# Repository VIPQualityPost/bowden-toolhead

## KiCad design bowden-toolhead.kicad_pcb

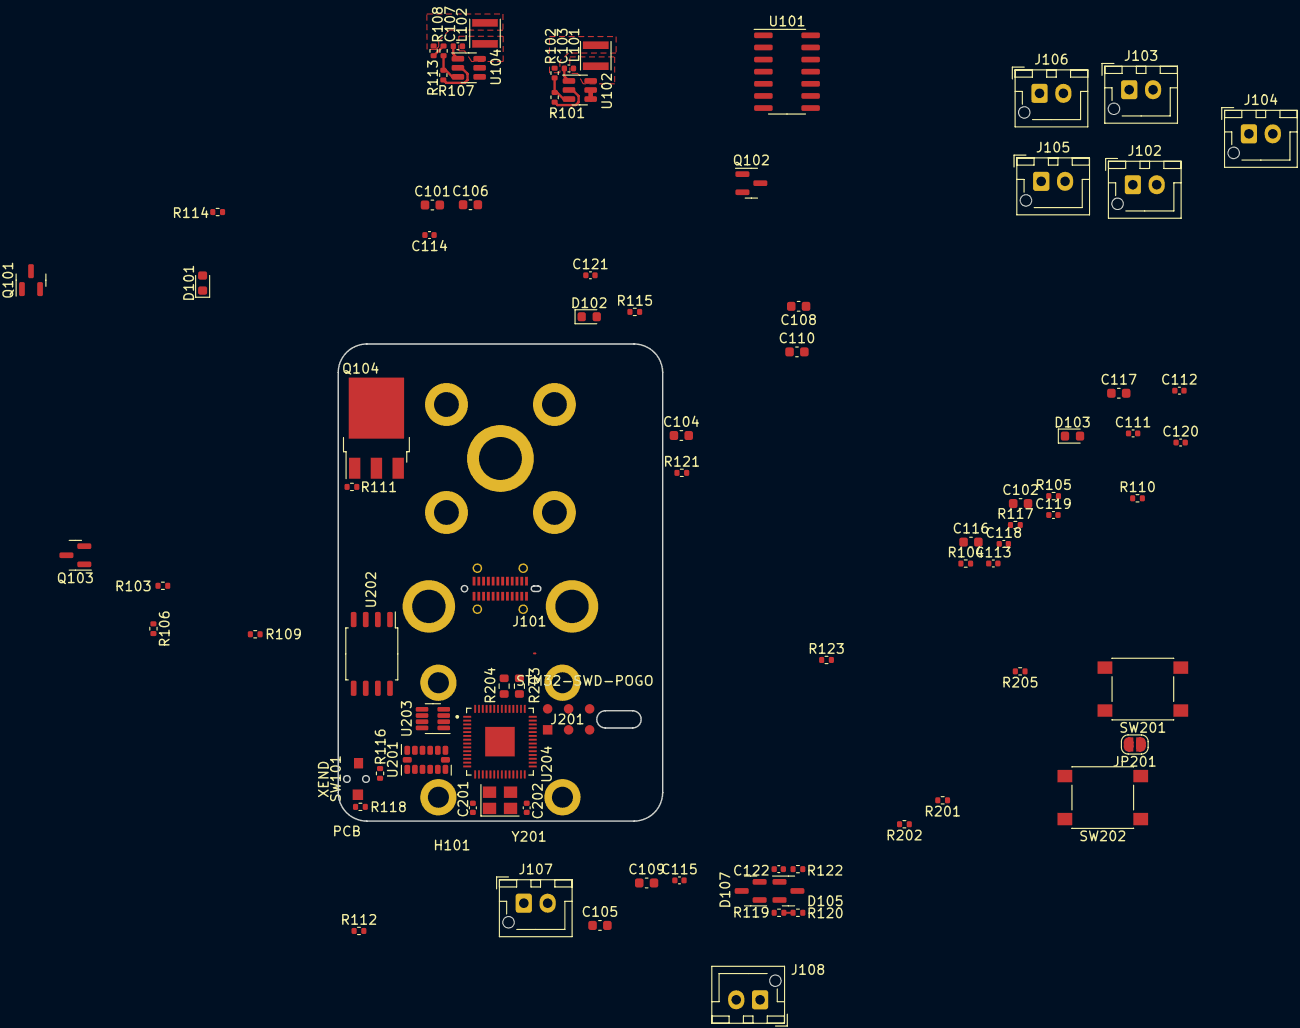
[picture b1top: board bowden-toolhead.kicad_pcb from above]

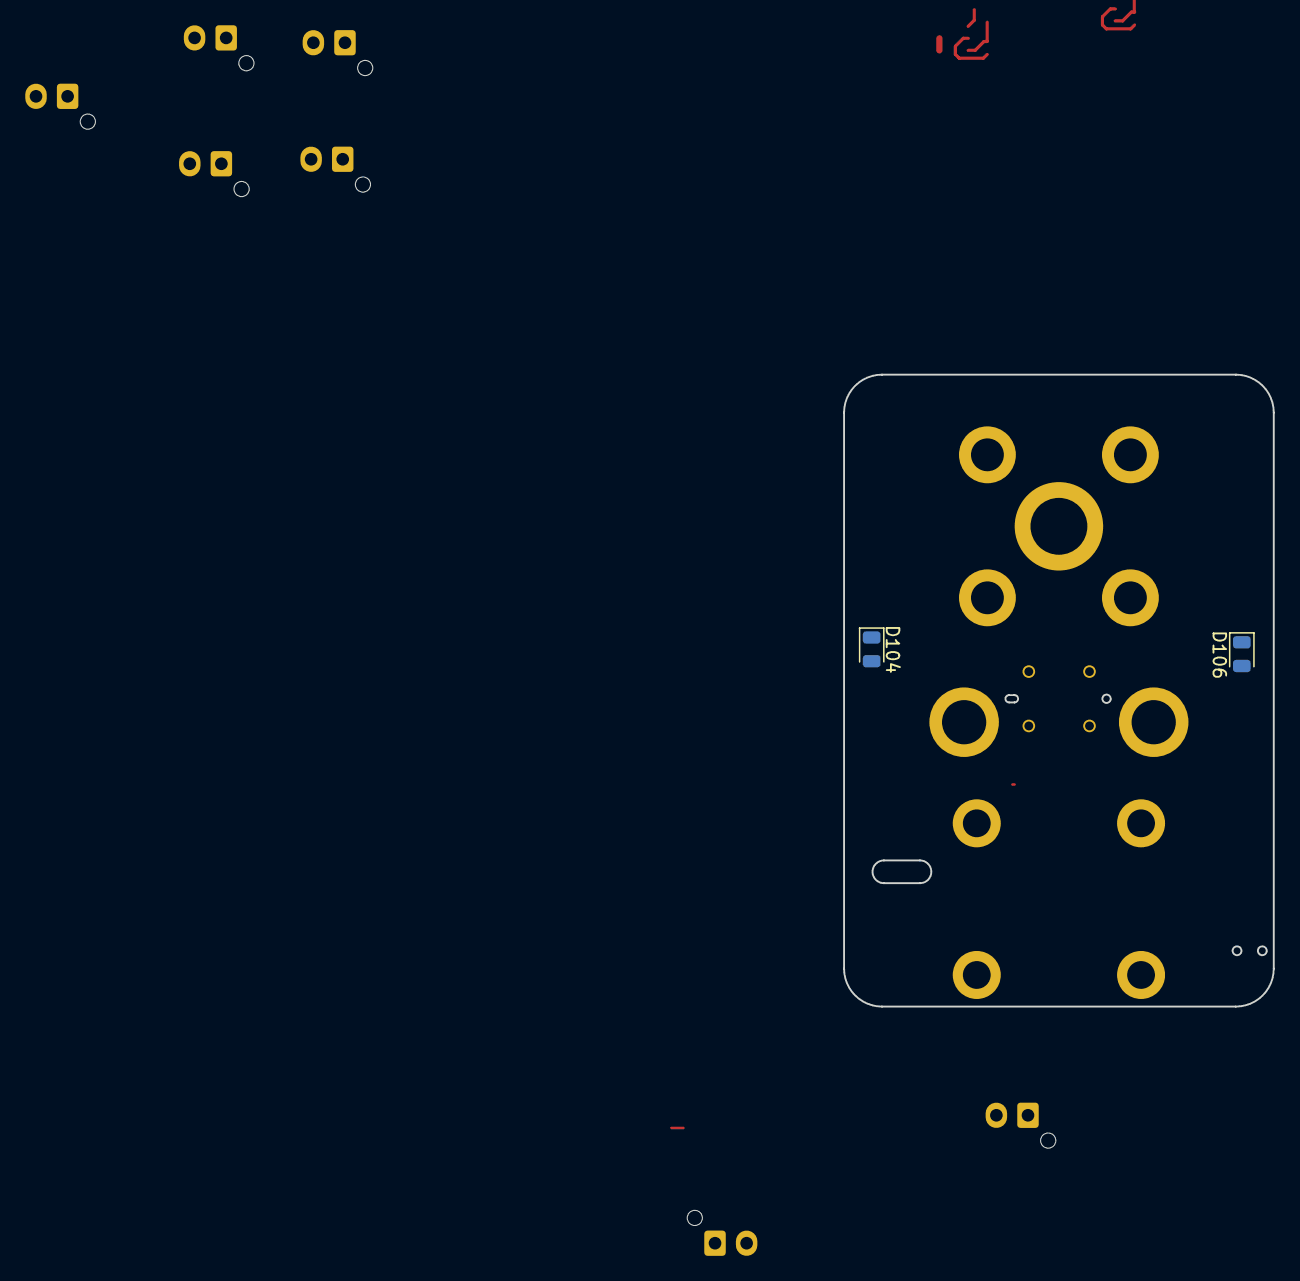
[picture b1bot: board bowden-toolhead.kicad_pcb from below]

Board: 2 copper layers, 34.0 x 50.0 mm, 87 parts (2 on the bottom side), 62 nets.

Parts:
C101, C102, C104, C105, C106, C108, C109, C110, C116, C117: 10uF; C_0603_1608Metric
C103, C107, C112, C114, C115, C120, C121, C122: 0.1uF; C_0402_1005Metric
C111, C113, C118, C119: 1uF; C_0402_1005Metric
C201, C202: 20pF; C_0402_1005Metric
D101, D102, D103: LED; LED_0603_1608Metric
D104, D106: LED; LED_0805_2012Metric
D105: BAV99; SOT-23
D107: 3V3; SOT-23
H101: PCB; v0-carriage-board
J101: 918-418K2022Y40004
J102: POWER; JST_XH_B2B-XH-AM_1x02_P2.50mm_Vertical
J103: PARTFAN_A; JST_XH_B2B-XH-AM_1x02_P2.50mm_Vertical
J104: PARTFAN_B; JST_XH_B2B-XH-AM_1x02_P2.50mm_Vertical
J105: CANBUS; JST_XH_B2B-XH-AM_1x02_P2.50mm_Vertical
J106: HEFAN; JST_XH_B2B-XH-AM_1x02_P2.50mm_Vertical
J107: HEATER; JST_XH_B2B-XH-AM_1x02_P2.50mm_Vertical
J108: THERM0; JST_XH_B2B-XH-AM_1x02_P2.50mm_Vertical
J201: STM32-SWD-POGO; SWD_pogo_landing
JP201: node term; SolderJumper-2_P1.3mm_Open_RoundedPad1.0x1.5mm
L101, L102: 4.7uH; L_Taiyo-Yuden_NR-30xx
Q101, Q102, Q103: AO3400A; SOT-23
Q104: NCE6020AK; TO-252-3_TabPin2
R101, R104, R106, R107, R110, R112, R202: 10k; R_0402_1005Metric
R102: 51k; R_0402_1005Metric
R103, R105, R109, R111, R118, R201: 120R; R_0402_1005Metric
R108: 27k; R_0402_1005Metric
R113: 3.9k; R_0402_1005Metric
R114: 3.3k; R_0402_1005Metric
R115: 5.1k; R_0402_1005Metric
R116: DNP; R_0402_1005Metric
R117: 24k; R_0402_1005Metric
R119: 4.7k; R_0402_1005Metric
R120, R122: 2.4k; R_0402_1005Metric
R121, R123, R205: 1k; R_0402_1005Metric
R203, R204: 27R; R_0603_1608Metric
SW101: XEND; D3SH-boss
SW201: RESET; SW_Push_1P1T_NO_6x6mm_H9.5mm
SW202: BOOTSEL; SW_Push_1P1T_NO_6x6mm_H9.5mm
U101: 74LS125; SOIC-14_3.9x8.7mm_P1.27mm
U102, U104: RY8310; SOT-23-6
U201: ADXL345; LGA-14_3x5mm_P0.8mm_LayoutBorder1x6y
U202: W25Q32JVSS; SOIC-8_5.23x5.23mm_P1.27mm
U203: MAX3051; SOT-23-8
U204: RP2040; QFN40P700X700X90-57N
Y201: 12MHz; Crystal_SMD_3225-4Pin_3.2x2.5mm

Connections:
+3V3: C108.1, C110.2, C113.2, C115.2, C117.2, C119.2, C121.2, D105.2 (A), J201.1, L102.2, R113.2, R114.1, R116.1, R119.1, R202.2, U201.1 (Vdd_I/O), U201.6 (Vs), U202.8 (VCC), U203.3 (VDD), U204.1 (IOVDD), U204.10 (IOVDD), U204.22 (IOVDD), U204.33 (IOVDD), U204.42 (IOVDD), U204.43 (ADC_AVDD), U204.44 (VREG_VIN), U204.48 (USB_VDD), U204.49 (IOVDD)
+5V: C104.1, C116.1, C118.1, C120.1, L101.2, R102.2, R115.1, R121.1, R123.1, U101.14 (VCC)
/3v3sw: C107.2, L102.1, U104.6 (SW)
/5Vsw: C103.2, L101.1, U102.6 (SW)
CAN_HI: J105.1, JP201.2 (B), U203.7 (CANH)
CAN_LO: J105.2, R201.1, U203.6 (CANL)
CAN_RX: U203.4 (RXD), U204.7 (GPIO5)
CAN_TX: U203.1 (TXD), U204.6 (GPIO4)
GND: C101.2, C102.2, C104.2, C105.2, C106.2, C108.2, C109.2, C110.1, C111.2, C112.2, C113.1, C114.2, C115.1, C116.2, C117.1, C118.2, C119.1, C120.2, C121.1, C122.1, C201.1, C202.2, D101.1 (K), D102.1 (K), D103.1 (K), D105.1 (K), D107.2 (A2), J101.A1 (GND), J101.A12 (GND), J101.B1 (GND), J101.B12 (GND), J101.S1 (SHIELD), J102.2, J103.2, J104.2, J106.2, J107.2, J108.2, J201.5, Q101.2 (S), Q102.2 (S), Q103.2 (S), Q104.3 (S), R101.2, R104.2, R106.2, R107.2, R110.2, R112.2, R205.1, SW101.2 (B), SW201.2, U101.1, U101.4, U101.7 (GND), U101.10, U101.13, U102.2 (GND), U104.2 (GND), U201.2 (GND), U201.4 (GND), U201.5 (GND), U202.4 (GND), U203.2 (GND), U203.5 (SHDN), U203.8 (RS), U204.19 (TESTEN), U204.57 (GND), Y201.2, Y201.4
HEATER: J107.1, Q104.2 (D)
HEATER_MCU: U101.12, U204.31 (GPIO20)
HEFAN: J106.1, Q101.3 (D)
HEFAN_MCU: U101.2, U204.27 (GPIO16)
LED: D104.1 (K), D106.1 (K), Q103.3 (D)
LED_MCU: U101.9, U204.34 (GPIO22)
unnamed: C103.1, U102.1 (BST)
unnamed: C107.1, U104.1 (BST)
unnamed: D101.2 (A), R114.2
unnamed: D102.2 (A), R115.2
unnamed: D103.2 (A), R117.2
unnamed: D104.2 (A), R121.2
unnamed: D105.3 (K), R120.1, R122.2
unnamed: D106.2 (A), R123.2
unnamed: JP201.1 (A), R201.2
unnamed: Q101.1 (G), R103.2
unnamed: Q102.1 (G), R105.2
unnamed: Q103.1 (G), R109.2
unnamed: Q104.1 (G), R111.2
unnamed: R101.1, R102.1, U102.3 (FB)
unnamed: R103.1, R104.1, U101.3
unnamed: R105.1, R106.1, U101.6
unnamed: R107.1, R108.1, U104.3 (FB)
unnamed: R108.2, R113.1
unnamed: R109.1, R110.1, U101.8
unnamed: R111.1, R112.1, U101.11
unnamed: R118.2, SW101.1 (A)
unnamed: R203.1, U204.46 (USB_DM)
unnamed: R204.1, U204.47 (USB_DP)
unnamed: R205.2, SW202.2
unnamed: U204.23 (DVDD), U204.45 (VREG_VOUT), U204.50 (DVDD)
PARTFAN: J103.1, J104.1, Q102.3 (D)
PARTFAN_MCU: U101.5, U204.29 (GPIO18)
QSPI_CS: U202.1 (~CS), U204.56 (QSPI_CSN)
QSPI_D0: U202.5 (DI(IO0)), U204.53 (QSPI_SD0)
QSPI_D1: U202.2 (DO(IO1)), U204.55 (QSPI_SD1)
QSPI_D2: U202.3 (IO2), U204.54 (QSPI_SD2)
QSPI_D3: U202.7 (IO3), U204.51 (QSPI_SD3)
QSPI_SCLK: SW202.1, U202.6 (CLK), U204.52 (QSPI_SCLK)
RUN: J201.3, R202.1, SW201.1, U204.26 (RUN)
SPI1_CS_ADXL: U201.7 (~CS), U204.12 (GPIO9)
SPI1_RX: U201.12 (SDO/ADDR), U204.11 (GPIO8)
SPI1_SCK: U201.14 (SCL/SCLK), U204.13 (GPIO10)
SPI1_TX: U201.13 (SDA/SDI/SDIO), U204.14 (GPIO11)
SWD: J201.2, U204.25 (SWD)
THERM0: J108.1, R119.2, R120.2
THERM0_MCU: C122.2, D107.1 (A1), R122.1, U204.38 (GPIO26/ADC0)
USB_M: J101.A7 (D-), J101.B7 (D-), R203.2
USB_P: J101.A6 (D+), J101.B6 (D+), R204.2
VBUS: C101.1, C102.1, C105.1, C106.1, C109.1, C111.1, C114.1, J102.1, R117.1, U102.4 (EN), U102.5 (VIN), U104.4 (EN), U104.5 (VIN)
XEND: C112.1, R116.2, R118.1, U204.17 (GPIO14)
XIN: C201.2, U204.20 (XIN), Y201.1
XOUT: C202.1, U204.21 (XOUT), Y201.3

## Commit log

2022-11-18 initial files
2022-11-30 work on layout
2023-02-13 Auto-commit Mon Feb 13 12:20:09 EST 2023
2023-02-17 Auto-commit Thu Feb 16 21:34:59 EST 2023
2023-02-17 Auto-commit Fri Feb 17 11:26:33 EST 2023
2023-02-17 Auto-commit Fri Feb 17 12:27:48 EST 2023
2023-02-17 Auto-commit Fri Feb 17 13:04:05 EST 2023
2023-02-17 Remove ignored files
